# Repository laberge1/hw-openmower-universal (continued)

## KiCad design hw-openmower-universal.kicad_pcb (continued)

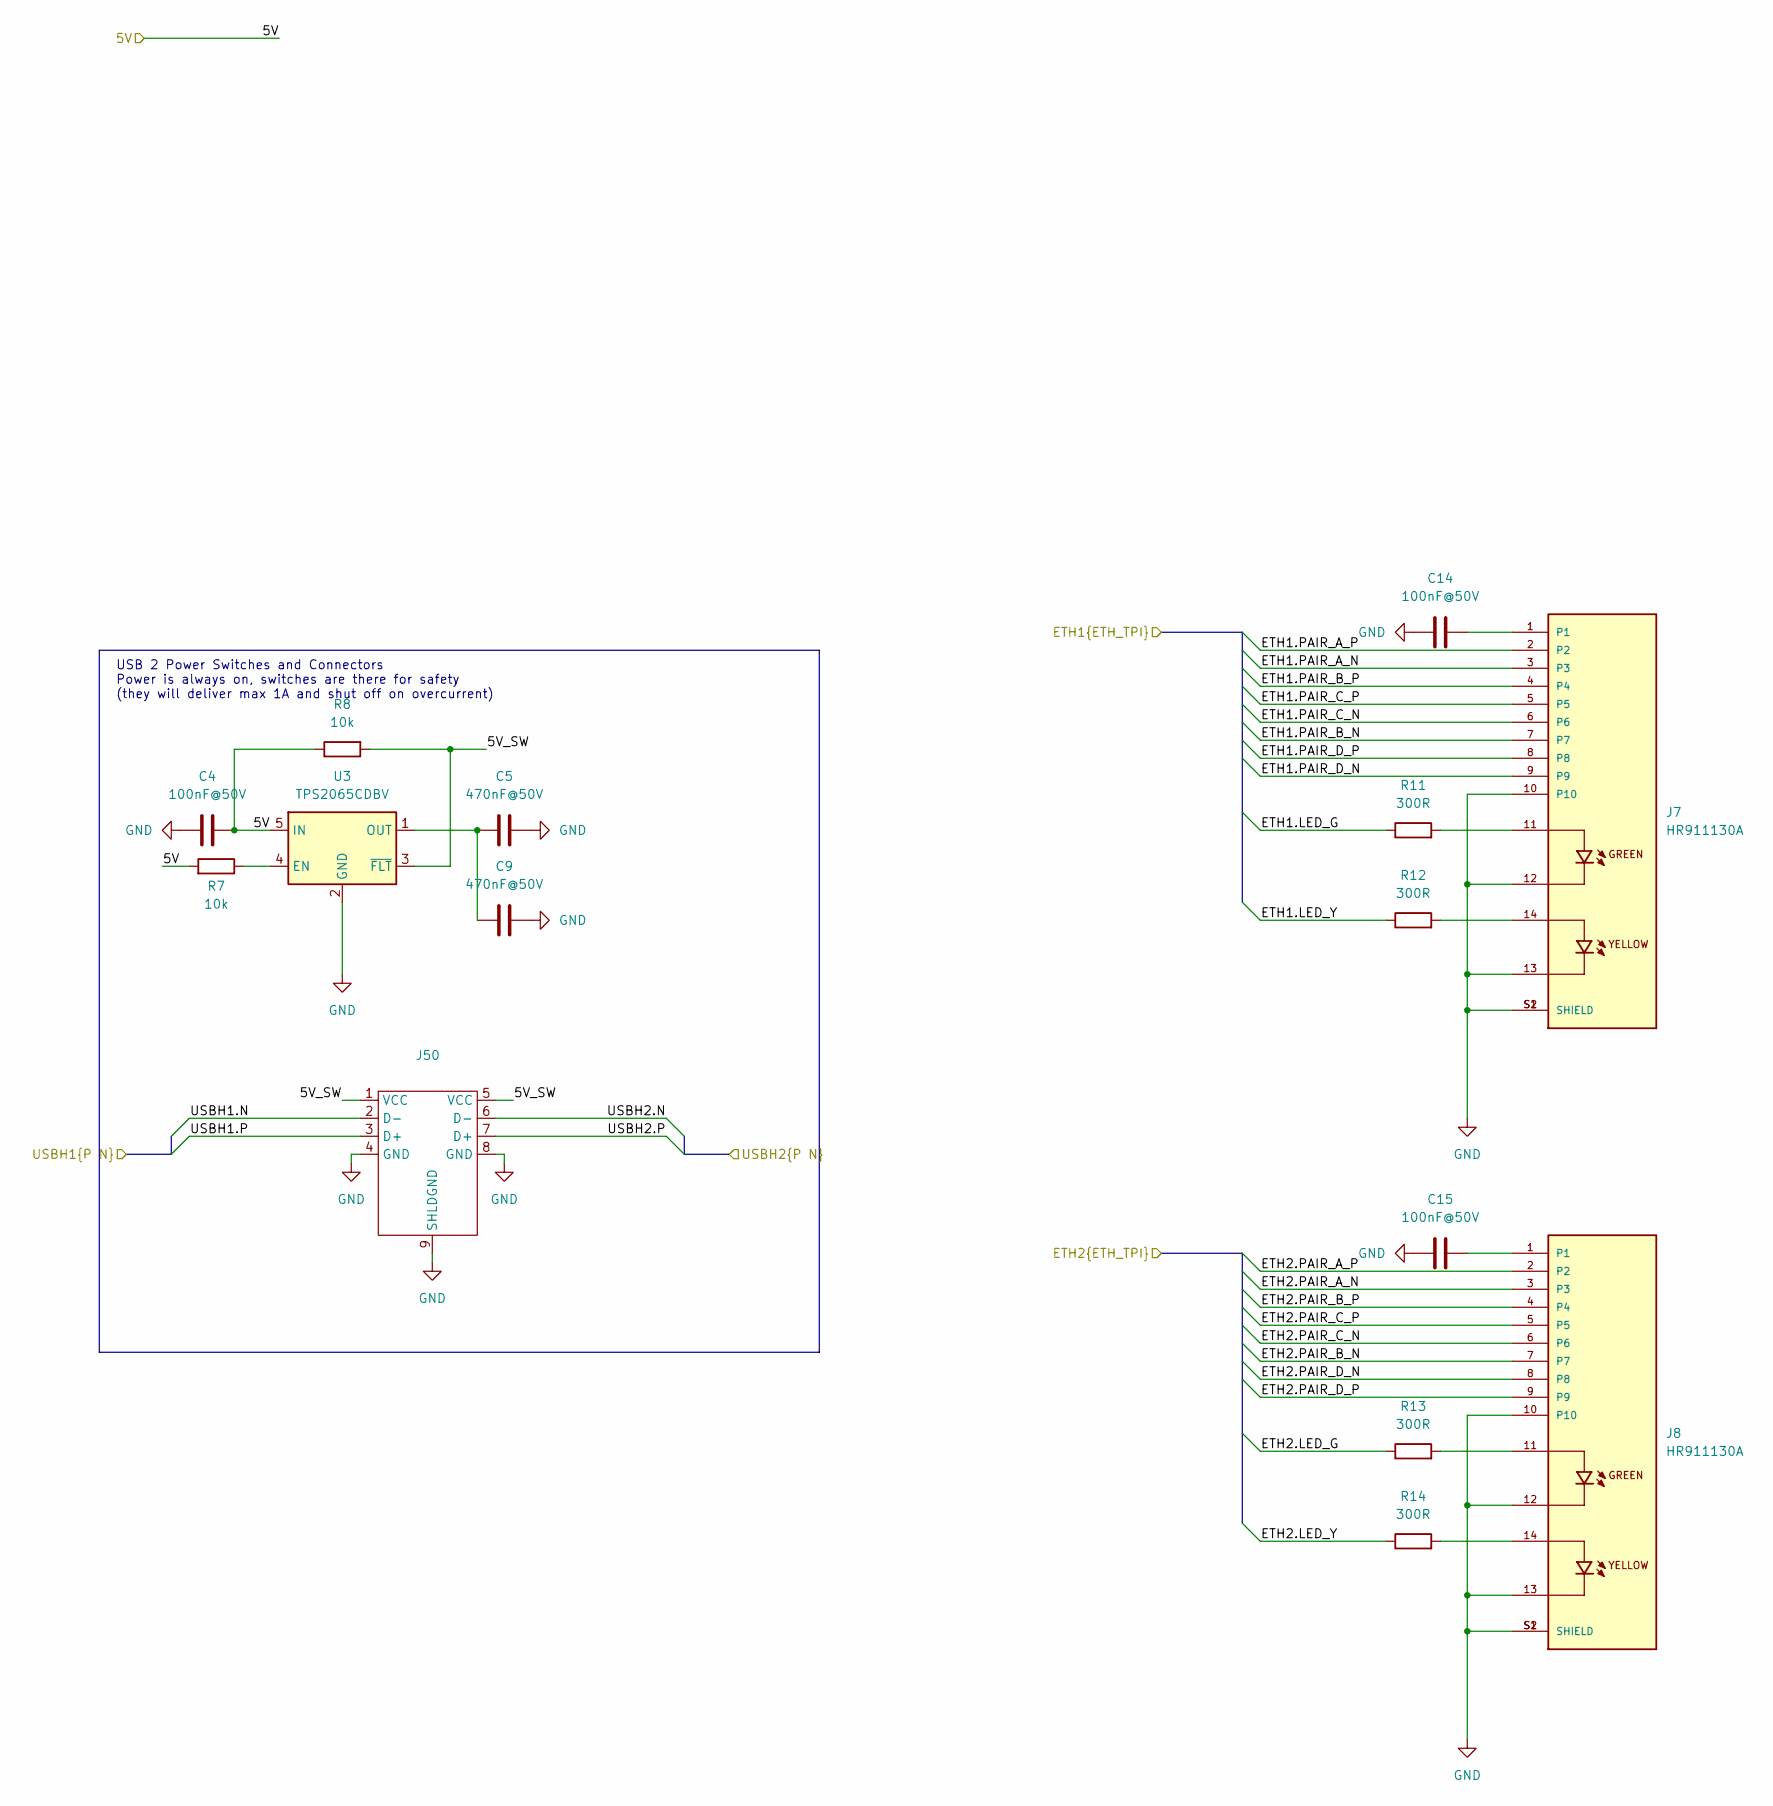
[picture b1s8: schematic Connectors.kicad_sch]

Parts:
C4, C14, C15: 100nF@50V; C_0402_1005Metric; JLC C307331
C5, C9: 470nF@50V; C_0805_2012Metric; JLC C13967
J7, J8: HR911130A; PARTREV A; JLC C54408
J50: Kinghelm_USB_dual_vert
R7, R8: 10k; R_0402_1005Metric; JLC C25744
R11, R12, R13, R14: 300R; R_0603_1608Metric; JLC C23025
U3: TPS2065CDBV; SOT-23-5; JLC C353882

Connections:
/5V: C4.1, R7.2, R8.1, U3.5 (IN); also elsewhere on the board
/subpcb_logic/Connectors/5V_SW: J50.1 (VCC), J50.5 (VCC), R8.2, U3.3 (~FLT)
/subpcb_logic/Connectors/ETH1.LED_G: R11.1; also elsewhere on the board
/subpcb_logic/Connectors/ETH1.LED_Y: R12.1; also elsewhere on the board
/subpcb_logic/Connectors/ETH1.PAIR_A_N: J7.3; also elsewhere on the board
/subpcb_logic/Connectors/ETH1.PAIR_A_P: J7.2; also elsewhere on the board
/subpcb_logic/Connectors/ETH1.PAIR_B_N: J7.7; also elsewhere on the board
/subpcb_logic/Connectors/ETH1.PAIR_B_P: J7.4; also elsewhere on the board
/subpcb_logic/Connectors/ETH1.PAIR_C_N: J7.6; also elsewhere on the board
/subpcb_logic/Connectors/ETH1.PAIR_C_P: J7.5; also elsewhere on the board
/subpcb_logic/Connectors/ETH1.PAIR_D_N: J7.9; also elsewhere on the board
/subpcb_logic/Connectors/ETH1.PAIR_D_P: J7.8; also elsewhere on the board
/subpcb_logic/Connectors/ETH2.LED_G: R13.1; also elsewhere on the board
/subpcb_logic/Connectors/ETH2.LED_Y: R14.1; also elsewhere on the board
/subpcb_logic/Connectors/ETH2.PAIR_A_N: J8.3; also elsewhere on the board
/subpcb_logic/Connectors/ETH2.PAIR_A_P: J8.2; also elsewhere on the board
/subpcb_logic/Connectors/ETH2.PAIR_B_N: J8.7; also elsewhere on the board
/subpcb_logic/Connectors/ETH2.PAIR_B_P: J8.4; also elsewhere on the board
/subpcb_logic/Connectors/ETH2.PAIR_C_N: J8.6; also elsewhere on the board
/subpcb_logic/Connectors/ETH2.PAIR_C_P: J8.5; also elsewhere on the board
/subpcb_logic/Connectors/ETH2.PAIR_D_N: J8.8; also elsewhere on the board
/subpcb_logic/Connectors/ETH2.PAIR_D_P: J8.9; also elsewhere on the board
/subpcb_logic/Connectors/USBH1.N: J50.2 (D-); also elsewhere on the board
/subpcb_logic/Connectors/USBH1.P: J50.3 (D+); also elsewhere on the board
/subpcb_logic/Connectors/USBH2.N: J50.6 (D-); also elsewhere on the board
/subpcb_logic/Connectors/USBH2.P: J50.7 (D+); also elsewhere on the board
GND: C4.2, C5.2, C9.2, C14.1, C15.1, J7.10, J7.12, J7.13, J7.S1 (SHIELD), J7.S2 (SHIELD), J8.10, J8.12, J8.13, J8.S1 (SHIELD), J8.S2 (SHIELD), J50.4 (GND), J50.8 (GND), J50.9 (SHLDGND), U3.2 (GND); also elsewhere on the board
unnamed: C14.2, J7.1
unnamed: J7.11, R11.2
unnamed: J7.14, R12.2
unnamed: C15.2, J8.1
unnamed: J8.11, R13.2
unnamed: J8.14, R14.2
unnamed: R7.1, U3.4 (EN)
unnamed: C5.1, C9.1, U3.1 (OUT)

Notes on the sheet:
USB 2 Power Switches and Connectors Power is always on, switches are there for safety (they will deliver max 1A and shut off on overcurrent)

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
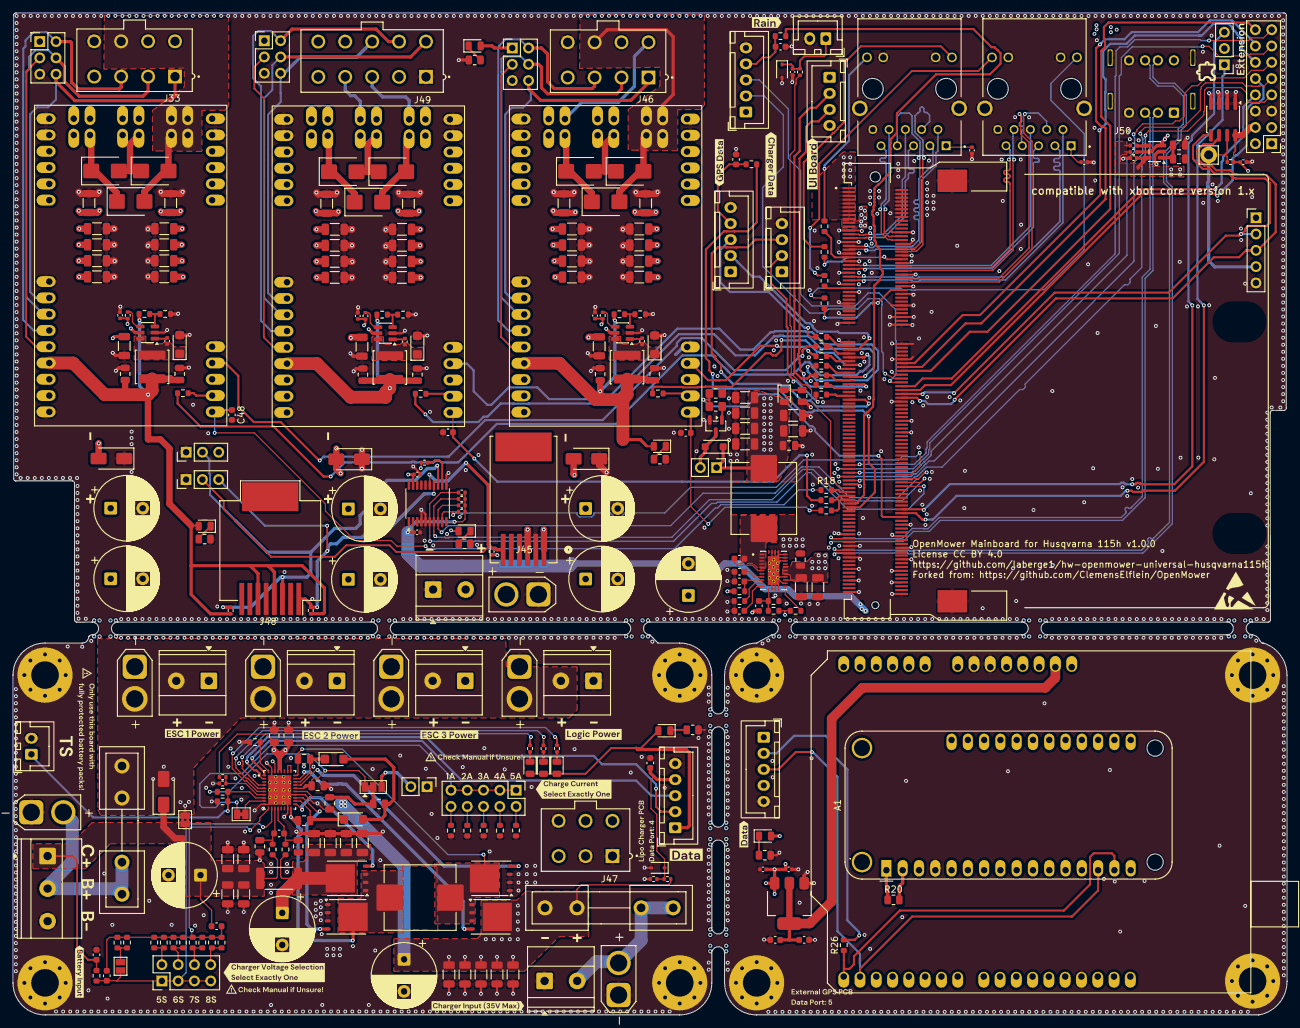
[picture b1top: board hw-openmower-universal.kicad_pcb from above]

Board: 4 copper layers, 198.7 x 156.3 mm, 409 parts (0 on the bottom side), 202 nets.

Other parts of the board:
B2, B3, B4, B5, B6, B7, B8, B9: MouseBite; MouseBite-Slot_2.0x2.0mm_inset_D0.5mm_P0.85mm_4h_Trace
C22, C23: 10uF@50V; C_1206_3216Metric
C24, C118: 470nF@50V; C_0805_2012Metric
C25, C28: C; C_0603_1608Metric
C26: 2.2uF/16V; C_0603_1608Metric
C27: 470nF/25V; C_0603_1608Metric
C29, C30, C31, C32, C33, C117: 47uF/10V; C_1206_3216Metric
C115: 1uF@50V; C_0603_1608Metric
D15: LED GREEN; LED_0805_2012Metric
L1: 6.8uH; L_Sunlord_MWSA1004S
LOGO2: ESD-Logo_6.6x6mm_SilkScreen
R51: R; R_0603_1608Metric
R56: 100k; R_0603_1608Metric
R57: 100k 0.1%; R_0603_1608Metric
R61: 25k 0.1%; R_0603_1608Metric
R62: 1k; R_0805_2012Metric
R82: 0R; R_0603_1608Metric
U11: LM76005RNPR
kibuzzard-670E8F90: G***; kibuzzard-670E8F90
kibuzzard-670E90ED, kibuzzard-670E90ED#2: G***; kibuzzard-670E90ED
kibuzzard-670E91C7: G***; kibuzzard-670E91C7
kibuzzard-670E91D3: G***; kibuzzard-670E91D3
kibuzzard-670E91D8: G***; kibuzzard-670E91D8
kibuzzard-670E91E3: G***; kibuzzard-670E91E3
kibuzzard-6711AB8A: G***; kibuzzard-6711AB8A
kibuzzard-6853DB1B: G***; kibuzzard-6853DB1B
kibuzzard-6853DB41: G***; kibuzzard-6853DB41
kibuzzard-6853DBB6: G***; kibuzzard-6853DBB6
kibuzzard-67111AE1: G***; kibuzzard-67111AE1
kibuzzard-67111D43: G***; kibuzzard-67111D43
kibuzzard-67111FCC: G***; kibuzzard-67111FCC
kibuzzard-67111FDF: G***; kibuzzard-67111FDF
kibuzzard-67111FEA: G***; kibuzzard-67111FEA
kibuzzard-67111FFB: G***; kibuzzard-67111FFB
kibuzzard-68532E1B, kibuzzard-68532E1B#2, kibuzzard-68532E1B#3, kibuzzard-68532E1B#4, kibuzzard-68532E1B#5, kibuzzard-68532E1B#6, kibuzzard-68532E1B#7, kibuzzard-68532E1B#8, kibuzzard-68532E1B#9: G***; kibuzzard-68532E1B
kibuzzard-68532E12, kibuzzard-68532E12#2, kibuzzard-68532E12#3, kibuzzard-68532E12#4, kibuzzard-68532E12#5, kibuzzard-68532E12#6, kibuzzard-68532E12#7, kibuzzard-68532E12#8, kibuzzard-68532E12#9: G***; kibuzzard-68532E12
kibuzzard-671117D8: G***; kibuzzard-671117D8
kibuzzard-671119EE: G***; kibuzzard-671119EE
kibuzzard-671124D1: G***; kibuzzard-671124D1
kibuzzard-671124D9: G***; kibuzzard-671124D9
kibuzzard-671188B5: G***; kibuzzard-671188B5
kibuzzard-671188C2: G***; kibuzzard-671188C2
kibuzzard-671188D3: G***; kibuzzard-671188D3
kibuzzard-671188DE: G***; kibuzzard-671188DE
kibuzzard-671188EA: G***; kibuzzard-671188EA
kibuzzard-6711201C: G***; kibuzzard-6711201C
kibuzzard-6716385D: G***; kibuzzard-6716385D
kibuzzard-6716388B: G***; kibuzzard-6716388B
kibuzzard-67111882: G***; kibuzzard-67111882
kibuzzard-67111937: G***; kibuzzard-67111937
kibuzzard-67111945: G***; kibuzzard-67111945
kibuzzard-67163896: G***; kibuzzard-67163896

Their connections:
/5V: C28.1, C29.1, C30.1, C31.1, C32.1, C33.1, C117.1, C118.1, D15.2 (A), L1.2, R56.2, R57.1, R82.1; also elsewhere on the board
/V_BATTERY: C22.1, C23.1, C24.1, U11.18 (EN), U11.20 (PVIN), U11.21 (PVIN), U11.22 (PVIN); also elsewhere on the board
/subpcb_logic/DCDC/BIAS: C115.2, R82.2, U11.9 (BIAS)
GND: C22.2, C23.2, C24.2, C25.2, C26.1, C29.2, C30.2, C31.2, C32.2, C33.2, C115.1, C117.2, C118.2, R51.2, R61.2, R62.2, U11.13 (AGND), U11.14 (AGND), U11.15 (AGND), U11.17 (SYNC/MODE), U11.19 (NC), U11.24 (PGND), U11.25 (PGND), U11.26 (PGND), U11.27 (NC), U11.28 (NC), U11.29 (NC), U11.30 (NC), U11.31 (EP); also elsewhere on the board
unnamed: C27.2, L1.1, U11.1 (SW), U11.2 (SW), U11.3 (SW), U11.4 (SW), U11.5 (SW)
unnamed: D15.1 (K), R62.1
unnamed: C27.1, U11.6 (BOOT)
unnamed: C28.2, R57.2, R61.1, U11.12 (FB)
unnamed: R56.1, U11.16 (PGOOD)
unnamed: R51.1, U11.10 (RT)
unnamed: C25.1, U11.11 (SS/TRK)
unnamed: C26.2, U11.8 (VCC)

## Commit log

2026-02-09 New conns for xESC
    Added new connectors into the design for motors.
2026-03-07 Routing progress and vertical USB
2026-03-08 Additional routing updates
2026-03-10 Incremental routing updates
2026-03-13 Additional routing
2026-03-23 Routing progress
2026-04-07 Further routing progress
2026-04-20 Review ready layout
    DRC mostly clean. Need to add GND via stitching and GND return vias yet, and general review
2026-05-27 v1.0.0 - released to manufacturing
    Released to manufacturing on 5/27/2026
